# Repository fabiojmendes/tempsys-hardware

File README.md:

<!-- vim: set tw=80: -->

# Tempsys hardware

Kicad hardware design for the Tempsys board.

## Block diagram

## Schematics

The board is built around the
[E73-2G4M08S1C](https://www.cdebyte.com/products/E73-2G4M08S1C) module that
relies on the nRF52840 chip from Nordic. The hardware design is minimalistic to
avoid any unnecessary power draw.

In short:

- An external XTAL is used to further reduce power consumption.
- Pull-up resistors on the i2c bus.
- Programming headers are provided.
- Reset button.
- Extra GPIO headers if necessary.
- CR-2032 battery holder.

## PCB

## Assembled product

Slightly older version of the PCB without the pull-up resistors.

## Current draw

The hardware is optimized to sip as little power as possible. Thanks to the
Nordic low power capabilities this device runs for more than a year on a single
coin cell battery CR-2032. In idle it consumes only ~3uA, and around 250uA when
the Bluetooth radio is engaged.

From the [firmware](https://github.com/fabiojmendes/tempsys-firmware)
perspective, all devices are set to sleep when not in use and the advertising
rate for the Bluetooth LE is stretched as much as possible.

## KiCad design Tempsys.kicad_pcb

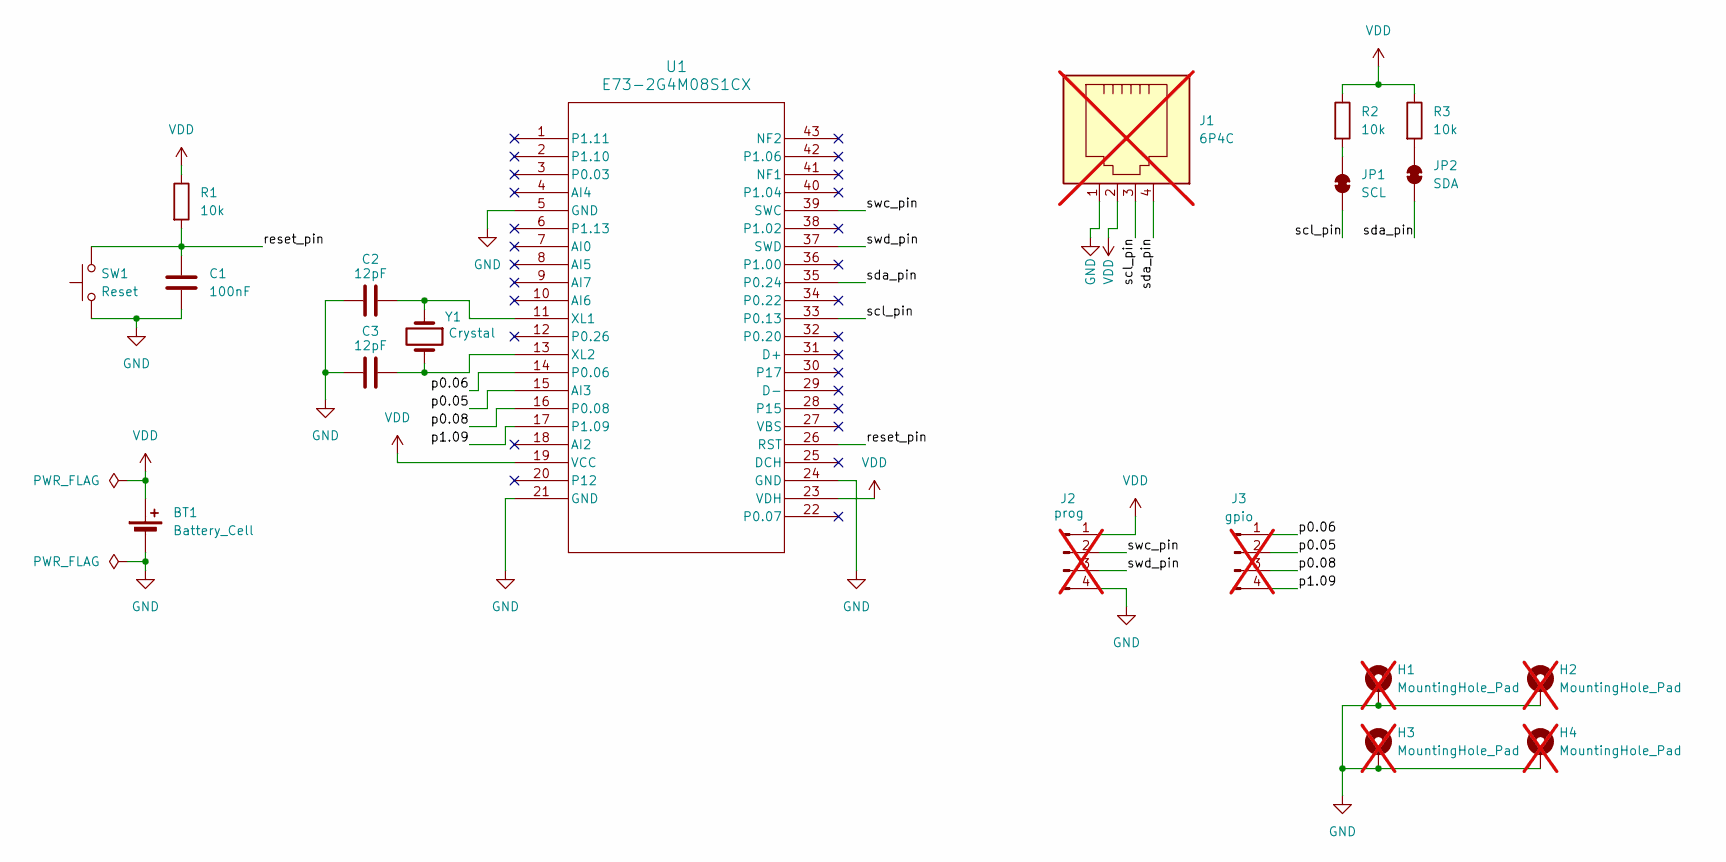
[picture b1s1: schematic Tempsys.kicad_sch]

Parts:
BT1: Battery_Cell; CR2032-BS-6-1; LCSC C70377
C1: 100nF; C_0402_1005Metric; LCSC C1525
C2, C3: 12pF; C_0402_1005Metric; LCSC C1547
H1, H2, H3, H4: MountingHole_Pad; MountingHole_2.2mm_M2_ISO7380_Pad; not fitted
J1: 6P4C; 438600003; LCSC C77856; not fitted
J2: prog; PinHeader_1x04_P2.54mm_Vertical; not fitted
J3: gpio; PinHeader_1x04_P2.54mm_Vertical; not fitted
JP1: SCL; SolderJumper-2_P1.3mm_Bridged_RoundedPad1.0x1.5mm
JP2: SDA; SolderJumper-2_P1.3mm_Bridged_RoundedPad1.0x1.5mm
R1, R2, R3: 10k; R_0402_1005Metric; LCSC C25744
SW1: Reset; SW_Push_1P1T_XKB_TS-1187A; LCSC C318884
U1: E73-2G4M08S1CX; E73(2G4M08S1C); LCSC C356849
Y1: Crystal; Crystal_SMD_3215-2Pin_3.2x1.5mm; LCSC C32346

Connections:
/p0.05: J3.2, U1.15 (AI3)
/p0.06: J3.1, U1.14 (P0.06)
/p0.08: J3.3, U1.16 (P0.08)
/p1.09: J3.4, U1.17 (P1.09)
/reset_pin: C1.1, R1.2, SW1.2, U1.26 (RST)
/scl_pin: J1.3, JP1.1 (A), U1.33 (P0.13)
/sda_pin: J1.4, JP2.1 (A), U1.35 (P0.24)
/swc_pin: J2.2, U1.39 (SWC)
/swd_pin: J2.3, U1.37 (SWD)
GND: BT1.2 (-), C1.2, C2.2, C3.2, H1.1, H2.1, H3.1, H4.1, J1.1, J2.4, SW1.1, U1.5 (GND), U1.21 (GND), U1.24 (GND)
unnamed: JP1.2 (B), R2.2
unnamed: JP2.2 (B), R3.2
unnamed: C2.1, U1.11 (XL1), Y1.1
unnamed: C3.1, U1.13 (XL2), Y1.2
VDD: BT1.1 (+), J1.2, J2.1, R1.1, R2.1, R3.1, U1.19 (VCC), U1.23 (VDH)

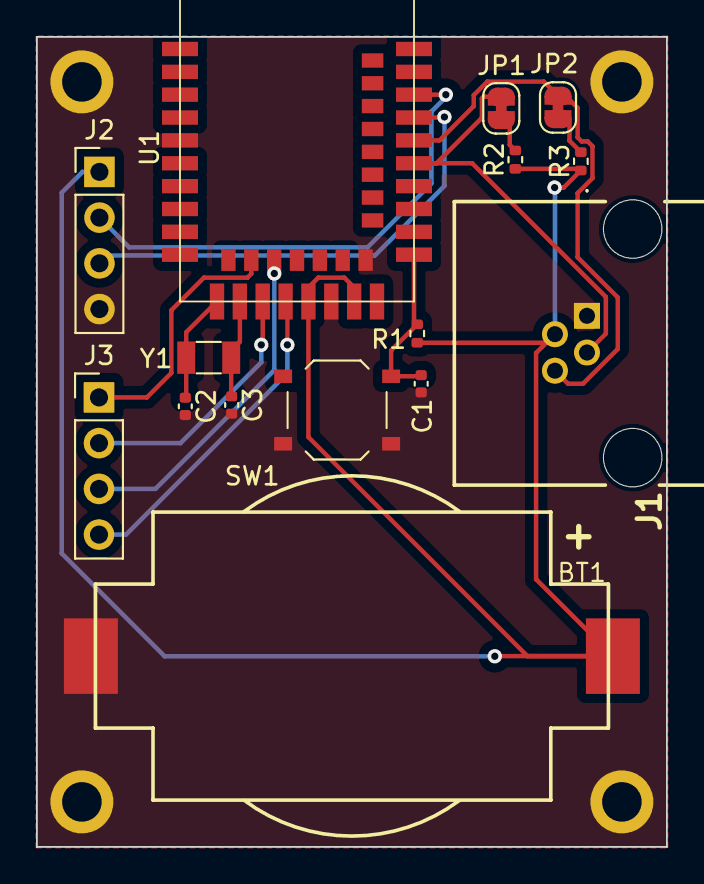
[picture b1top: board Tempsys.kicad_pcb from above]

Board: 2 copper layers, 35.0 x 45.0 mm, 19 parts (0 on the bottom side), 15 nets.

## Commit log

2024-08-23 Adding molex connector 3d model
2024-08-30 Adding pull-ups and jumpers. Also fixing the RJ11 footprint
2024-09-30 Readme updates
2024-10-03 Clean up the document
2024-10-03 Fix header
2024-10-04 Add punctuation
2025-08-19 Update documentation
2025-09-02 Add block diagram
